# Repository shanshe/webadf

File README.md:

# webadf

An Amiga disk library that puts a disk in a real Amiga's floppy drive over WiFi.

Two halves that work together:

- **A web app** for keeping Amiga disk images. Upload them, have them identified
  against TOSEC, OpenRetro and Demozoo, organise them into collections, browse and
  edit the files inside a disk, and rewind a disk to any earlier version.
- **A drive replacement.** An RP2350 board plugs into the Amiga's floppy connector,
  behaves like a DD or HD floppy drive, and plays whichever disk you pick in the web app.
  When the Amiga saves, the changes go back to the library.

Pick a disk in the browser, or tap its NFC tag on the drive, and the Amiga reads it.
Workbench 3.1 boots from the board, games load, and saves made on the Amiga show up
in the web app as new versions of the disk.

*Rev B, designed by Shanshe: 34-pin floppy header, floppy power connector, OLED
display, buzzer, a 4-pin header (J4), and a Pimoroni Pico Plus 2 W.
The KiCad project is in `wifi-floppy/hardware/`; check it with `pnpm hw:verify` before
ordering. The current bench board is rev A2.*

## Features

### Library

- Upload `.adf`, `.adz`, `.dms` and `.hfe`; drop `.lha` and `.zip` archives onto a disk
  to pick files out of them.
- HD (1.76 MB) ADFs are recognised and tagged HD, and are disks like any other: browsed
  and edited in the browser, with full history. Blank HD disks can be made from the
  New disk panel.
- Each unique disk is stored once, however many times it is uploaded.
- Disks are identified against TOSEC, OpenRetro and Demozoo, and grouped into titles
  with cover art, screenshots, publisher, year and type.
- Collections, search as you type, and a layout that works on a phone.
- Create a blank formatted disk: 880 KB or 1.76 MB, OFS or FFS.
- Download any disk as an ADF.

### Inside a disk

- Browse the AmigaDOS filesystem in the browser: files, folders, free space.
- Add, rename, move and delete files and folders; drop a folder from your computer
  onto a disk; drag entries between folders.
- Every change is a new version. The history panel shows what changed in each
  version, lets you browse any old version, and restores one as a new version.
- HFE images (including long-track formats such as Turrican's) play read-only and can
  be extracted to an ADF when every sector decodes.

### The drive

- Set up from a phone: the board opens a WiFi setup page, you enter your network and
  a pairing code from the web app, and it joins your library.
- Mount and eject from the web app, from the drive chips in the header, or by
  tapping an NFC tag.
- Reads and writes on a real Amiga. Saves reach the library as new disk versions,
  including saves made while the board was offline.
- Works as DF0 or alongside a second drive as DF1.
- Plays HD disks: the board tells the Amiga it is an HD drive while an HD disk is in.
  Needs Kickstart 3.0 or later. Playing needs firmware 1.4.1 or later (the web app
  refuses to mount an HD disk on older firmware and says so); saving to an HD disk
  needs 1.5.0 (1.4.x keeps HD write-protected on the board whatever the web app
  says).
- Write protection can be switched from the web app while the disk is in the drive.
- OLED status display: WiFi strength, what it is doing, the disk's name and the
  current track. An activity LED blinks on reads.
- Updates its own firmware from the web app. Releases are signed, a failed update
  falls back to the previous firmware, and the board never updates while a disk is
  in the drive.

### NFC tags

- Tap a tag on the drive to mount its disk. Tapping another tag swaps disks; tapping
  the one already in the drive does nothing.
- Write any disk to a tag from its library card or game page: click the NFC icon,
  tap a tag on the drive, and the result appears in the browser.
- A tag only ever mounts disks from your own library.
- Reader: HW-147C (Si512), on the board's I2C bus next to the OLED.

## How it works

An Amiga floppy drive does not deliver blocks. It hands Paula a raw magnetic flux
stream and the Amiga decodes MFM in software, so a drive emulator has to produce flux
at the right rate, continuously, while the disk spins.

```
  browser  ──mount──▶  web app  ──encodes ADF → MFM──▶  device  ──flux──▶  Amiga
     ▲                    │                                │
     └──── new version ◀──┴── Postgres + blobs     RP2350 + 8 MB PSRAM ◀── NFC tag
```

The server encodes a 901,120-byte ADF into 2,027,536 bytes of Amiga MFM and the board
streams it: PIO emits 2 µs bitcells, DMA restarts each revolution and raises INDEX,
giving 300 rpm. The whole disk lives in PSRAM, so a seek is answered immediately
instead of over the network. The board streams flux rather than ADFs, which lets
flux formats such as HFE use the same path.

An HD disk is the exception. The server sends the board the ADF itself (a small
WFAD header, then 1,802,240 bytes), and the board encodes each track to MFM as the
head reaches it, in about 4 ms, well inside the head's settle time. A PIO program
answers the Amiga's drive-ID read on RDY with the HD ID while an HD disk is mounted.
When the Amiga saves to an HD disk, the board checks all 22 sectors of the written
track, keeps them as ADF bytes, and uploads those bytes as they are.

When the Amiga writes, the board decodes the written tracks, uploads them, and the
server records them as a new version of the disk. Versions are stored as sector
deltas.

## Status

| | |
|---|---|
| Web app: library, collections, identification, search | live |
| Upload `.adf` `.adz` `.dms` `.hfe`; `.lha`/`.zip` onto a disk | live |
| File editing inside a disk, blank disks, drag and drop | live |
| Disk history: browse and restore any version | live, restore verified on hardware |
| Device: setup portal, WiFi, TLS, pairing | verified on hardware |
| Mount and eject from the browser and the drive chips | verified on hardware |
| Reading on a real Amiga (Workbench 3.1, games) | verified on hardware |
| Writing on a real Amiga, saves reach the library | verified on hardware |
| Second drive (DF1) alongside the board | verified on hardware |
| HFE, including long-track (Turrican) | verified on hardware; weak-bit titles not yet tested |
| HD disks, read-only (Kickstart 3.0+) | verified on hardware (firmware 1.4.1, Kickstart 3.1) |
| HD disks: Amiga saves, history, browser editing, blank HD disks | built and host-tested (firmware 1.5.0, not yet published); bench checklist owed (HANDOFF 3ao) |
| Firmware updates from the web app | verified on hardware (current: 1.3.1; 1.4.0 built, not yet published) |
| NFC: tap to mount, write tags from the web | verified on hardware |
| Rev B board | in design (Shanshe) |

## Repository

| Path | What |
|---|---|
| `src/` | the Next.js app |
| `src/lib/adfmfm/` | ADF ⇄ Amiga MFM encoder, verified against Greaseweazle |
| `src/lib/adffs/` | AmigaDOS filesystem reader/writer (OFS/FFS) |
| `src/lib/archive/` | `.lha`, `.zip` and `.dms` decoders, all browser-side |
| `src/lib/hfe/` | HFE parsing, conversion for the board, ADF extraction |
| `src/lib/disk-history/` | sector deltas and the version chain behind history and restore |
| `src/lib/nfc/` | NFC tap and tag-writing rules and storage |
| `wifi-floppy/firmware/` | the RP2350 firmware (pico-sdk ≥ 2.3.0) |
| `wifi-floppy/hardware/` | the board (KiCad) |
| `docs/superpowers/specs/` | design specs, one per feature |
| `HANDOFF.md` | the engineering log: decisions, measurements, bench results |

## Running it

```bash
pnpm install
pnpm dev                  # needs .env.local: DATABASE_URL, BLOB_READ_WRITE_TOKEN,
                          # BETTER_AUTH_SECRET, BETTER_AUTH_URL
pnpm test                 # vitest, pure logic
pnpm e2e                  # playwright, against a real database
```

Firmware:

```bash
export PICO_SDK_PATH=/path/to/pico-sdk        # tag 2.3.0 or later
pnpm firmware:build
pnpm firmware:test                            # host tests, no board needed
pnpm firmware:publish --dry-run               # sign and register a release
```

Write a disk to an NFC tag from the command line:

```bash
pnpm nfc:write "Turrican II disk 1"           # then tap a tag on the drive
```

The setup access point uses the password **`wififloppy`** by default. Set
`PORTAL_AP_PASSWORD` at build time to change it. The pairing code from the web app is
what authorises a board to join a library.

Every push that touches the firmware is built by
[`.github/workflows/firmware.yml`](.github/workflows/firmware.yml), which runs the host
tests and publishes a `.uf2` with a `manifest.json` (version, commit, size, SHA-256).

## Verification

Each layer that talks to hardware or to an undocumented format is checked against an
independent implementation:

| | checked against |
|---|---|
| `pnpm adfmfm:diff` | Greaseweazle's `amigados` codec |
| `pnpm adffs:verify` | `xdftool` |
| `pnpm lha:verify` | the real `lha` binary |
| `pnpm dms:verify` | xDMS, the implementation ours was ported from |

## Licence

- **Software** (the web app, scripts and the wifi-floppy firmware source): [MIT](LICENSE).
- **Hardware** (`wifi-floppy/hardware/`, the board design): [CERN-OHL-P-2.0](wifi-floppy/hardware/LICENSE), the
  permissive open-hardware licence, so anyone can build, modify and sell their own boards. The rev B PCB layout is
  Shanshe's work, licensed this way with Shanshe's agreement; see
  [wifi-floppy/hardware/NOTICE.md](wifi-floppy/hardware/NOTICE.md).
- **Third-party code, the libraries in the firmware image, and acknowledgements**: see
  [THIRD-PARTY-NOTICES.md](THIRD-PARTY-NOTICES.md). The Wi-Fi driver bundled with the Pico SDK is licensed for use
  on Raspberry Pi chips (which this board is).

This project builds on Nano-Tek, OpenFlops, Keir Fraser's FlashFloppy and Greaseweazle, and the other work credited
in the notices file.

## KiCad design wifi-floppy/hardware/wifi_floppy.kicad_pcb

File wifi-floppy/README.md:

# WiFi Floppy Emulator (Amiga) — Pico 2 W

Gotek-style drive replacement that streams pre-encoded MFM tracks over
WiFi from your ADF webservice instead of reading a USB stick.

## Contents
- `hardware/schematic.svg` — full schematic (net names match the PCB)
- `hardware/wifi_floppy.kicad_pcb` — placed **and routed** 2-layer board,
  45°-only corners, B.Cu ground pour. Open directly in KiCad 7/8 and
  press `B` to refill the zone.
- `hardware/generate_pcb.py` — the generator that produced the board,
  including a DRC-lite checker (crossings, clearance ≥0.15 mm, 45° rule).
  Currently passes with 0 violations.
- `firmware/` — pico-sdk project (RP2350 / `PICO_BOARD=pimoroni_pico_plus2_w_rp2350`,
  pico-sdk >= 2.3.0 required — see "Firmware build requirements" below).

## Design
- **J1** 34-pin, Amiga internal pinout: pin 2 = /DSKCHG, pin 34 = /RDY
  (unlike PC drives where 34 is DSKCHG).
- **U2 74LVC541A** buffers all host-driven lines into the Pico
  (3.3 V part, 5 V-tolerant inputs). J1→A1..A8→GP2..GP9 are mapped in
  physical order, so the input routing is completely crossing-free.
- **Q1–Q6 BSS138** give open-drain outputs. They invert: **GPIO high =
  bus line pulled low**. Firmware and the PIO program already account
  for this (`OUT_ASSERT`).
- **Power**: 5 V from the Berg connector through D1 (SS14) into VSYS.
  Safe to co-power over USB while bench testing.
- PIO `flux_out` emits 2 µs bitcells (8 PIO cycles @ 4 MHz, clkdiv 37.5
  from 150 MHz), 750 ns read pulses; DMA restarts per revolution and
  raises a ~2 ms INDEX pulse at the wrap → exactly 300 rpm timing.
- 16-track LRU cache (~205 KB) + neighbour prefetch; a track is ~12.7 KB
  so a LAN fetch lands well inside a seek's settle time.

## Track server protocol — SUPERSEDED

**This section describes a protocol the firmware no longer speaks.** `http_fetch.c`,
which implemented `GET /tracks/<n>`, was deleted in plan 4a. The real device contract is
`GET /api/device/poll` (long-poll for desired state), `GET /api/device/image/<sha256>`
(the whole disk as a `WFMF` container, format defined in `image_loader.c`), and
`POST /api/device/status`. See `INTEGRATION.md` and
`docs/superpowers/specs/2026-08-29-device-plane-disk-change-design.md` §10 for the actual
contract. Kept below only as a historical note; do not implement against it.

```
GET /tracks/<n>        n = cyl*2 + side  (0..159)
 -> 200, body = [u32 LE bit_count][raw MFM bytes]
POST /tracks/<n>       (write-back, not implemented yet)
```
Encode server-side (ADF → Amiga MFM incl. 0x4489 syncs, odd/even split);
the firmware just plays bits. Suggested next step for the webservice.

## DSKCHG / RDY
`src/dskchg.c` re-implements FlashFloppy's Amiga-interface behaviour
(chgrst=step semantics, motor-edge drive-ID shifter, spin-up delay).
It's a from-scratch implementation of the observable behaviour, not a
code port. FlashFloppy is Keir Fraser's (https://github.com/keirf/flashfloppy,
Unlicense) and is credited in ../THIRD-PARTY-NOTICES.md.

## Firmware build requirements

- **pico-sdk >= 2.3.0.** `hardware_psram` (and this board's
  `PICO_PSRAM_CS_PIN`/`PICO_PSRAM_SIZE_BYTES` board-header support) landed in
  pico-sdk PR #2919, after the 2.2.0 release; 2.3.0 is the first tag that has
  it. `CMakeLists.txt` checks `PICO_SDK_VERSION_STRING` and fails the
  configure step with an explanation if `PICO_SDK_PATH` points at anything
  older.
- **`brew install arm-none-eabi-gcc` is not sufficient** — that formula ships
  GCC and libgcc but no newlib, so linking fails with `cannot find -lg`/`-lc`
  on the very first target. Use the official ARM GNU Toolchain instead (the
  `gcc-arm-embedded` cask, or the equivalent tarball from
  developer.arm.com/downloads/-/arm-gnu-toolchain-downloads) and make sure
  its `bin/` is on `PATH` ahead of any homebrew `arm-none-eabi-*` shims.
- **`PORTAL_AP_PASSWORD` must be set in the environment (plan 4b).** It becomes the WPA2
  PSK for the provisioning access point (see "Provisioning a board" below); CMake's
  configure step fails on purpose if it is unset or empty, because an invalid WPA2 PSK
  cannot be reported back to a console-less board at runtime. The full build command:

  ```bash
  export PATH="/Applications/ArmGNUToolchain/15.3.rel1/arm-none-eabi/bin:$PATH"
  export PORTAL_AP_PASSWORD=<your AP password>
  pnpm firmware:build
  ```

## Provisioning a board (plan 4b)

**Steps 1-3 are verified on hardware as of 2026-09-10; steps 4-5 are not.** The AP
comes up, iOS raises the sign-in sheet on its own, and the form renders at
192.168.4.1. Everything from pressing Save onwards — teardown, association,
registration — has still only ever run against the host suite. See "Honest caveats"
below.

A board with no WiFi credentials stored in flash — or one that has just failed to associate
three times in a row — raises its own WPA2 access point named `wifi-floppy-XXXX`, where
`XXXX` is the last two octets of the board's MAC address (so several boards on a bench stay
distinguishable). To provision it:

1. **Mint a pairing code in webadf.** From the web app, generate a device pairing code for
   the board (single-use, 10-minute TTL — if it expires before step 4, generate a new one).
2. **Join `wifi-floppy-XXXX`** from your phone or laptop, using the WPA2 password baked into
   that board's firmware image at build time (`PORTAL_AP_PASSWORD`, above — whoever built
   the firmware knows it).
3. **Open any page** in a browser on that device. The board's DNS responder answers every
   query with its own address and the HTTP server redirects every path to `/`, so a phone's
   captive-portal probe should bring the config form up on its own; if it does not, browse to
   `http://192.168.4.1/` directly.
4. **Enter three fields**: your real WiFi network's SSID, its password, and the pairing code
   from step 1. Submitting does not commit anything yet — the board drops its own AP,
   attempts to associate with what you typed, and only writes the credentials to flash on
   success. Your phone will briefly lose the `wifi-floppy-XXXX` network while this happens.
5. **On success**, the board joins your real network and proceeds to register with webadf
   using the pairing code; the AP does not come back. **On failure** (wrong password, or the
   network was not found — the form distinguishes the two), the AP returns with the reason
   and the form is ready to try again; re-enter all three fields, since none are echoed back.

**Recovery without reflashing.** If webadf later reports the board's token as revoked or the
device row is deleted, the board erases its stored token and returns to step 1 automatically
— generate a fresh pairing code and repeat steps 2–5. The same is true of a rejected
(expired or already-used) pairing code: the board returns to the portal rather than retrying
the dead code forever.

## Watching the log

```bash
tio /dev/cu.usbmodem*          # brew install tio; it reconnects across reboots
```

Output looks like this — uptime in seconds.milliseconds, then which core:

```
[    0.002] c0 wifi-floppy boot: pimoroni_pico_plus2_w_rp2350
[    0.481] c1 radio up (RM2)
[    0.494] c1 portal: raising AP
[   34.117] c0 MOTOR        a=1 b=0
[   34.119] c0 SEL          a=1 b=0
[   34.226] c0 STEP         a=1 b=0
[   34.229] c0 TRACK-SERVED a=2 b=101376
[   34.431] c0 INDEX        a=3168 b=0
```

Two entry points, and the difference is load-bearing. `wf_logf()` formats with
`vsnprintf` and is for core1 and core0's loop. `wf_trace()` takes an integer event code
and two integers — no formatting, no format string — so it is legal inside the flux DMA
handler, where a flash-resident string would not be. `wf_trace` is placed in SRAM with
`__not_in_flash_func` for the same reason `dma_irq` is.

**core0 drains, core1 only produces.** core0's service loop already sleeps 1 ms per
iteration and the bit-level work is PIO and DMA, so it has the slack to write to USB;
core1's loop blocks for tens of seconds inside a long-poll and would strand every core0
trace behind it. A useful consequence: a core1 hang still gets its last line out, which
is why `cyw43_arch_init` failing logs before it spins forever.

The ring holds 63 records (~7 KB of SRAM). When it fills it **drops newest and counts
them**, then prints `-- N record(s) dropped --` once the backlog clears. It never blocks
a producer: a logger that stalls the floppy service loop to report on the floppy service
loop would be worse than no logger. `PICO_STDIO_USB_STDOUT_TIMEOUT_US` is set to 1 ms in
`CMakeLists.txt`, against an SDK default of 500 ms, so an unattended USB port cannot
stall that loop either.

UART stdio stays off and must stay off: GP0 and GP1 are INDEX and CHNG on this board, so
enabling it would drive the floppy bus.

## Honest caveats
- **First run on real hardware: 2026-09-10.** A rev A2 board, partially populated
  (J1, J2 and U1 only), flashed with `wifi_floppy.uf2` and powered over USB. What that
  exercised, end to end, on real silicon:
  - the RP2350 boots the image, reaches `main()`, and launches core1
  - `cyw43_arch_init()` succeeds — the **RM2 radio works over SPI**, the single
    largest never-before-run piece
  - the AP comes up: `wifi-floppy-6A38`, WPA2-AES, SSID built from the chip's own MAC
  - **DHCP hands the phone an address, the DNS responder answers, and the HTTP server
    serves the form** at `192.168.4.1`
  - **iOS's captive-portal probe raises the sign-in sheet on its own** ("Wi-Fi med
    tilmelding"), which was explicitly on the unverified list
  - the page's `28:cd:c1:19:6a:38` and the SSID's `6A38` agree, so `main.c`'s
    `mac_address_string()` and `portal_net.c`'s SSID construction cross-check
  - no re-enumeration of the USB CDC device over several minutes: no crash loop

  **Still not run on hardware:** everything past pressing Save. AP teardown and the
  transition back to station mode, association with a real network, the confirmation
  page arriving before the AP drops, DHCP lease renewal after teardown, the 3-slot
  lease pool under real phone behaviour, Android's captive-portal probe, TLS, SNTP,
  device registration, and the whole floppy side — PIO cycle counts, DMA, PSRAM image
  load, bus timing — which remain desk-checked only. See
  `docs/decisions/2026-08-31-device-portal-rulings.md`'s hardware-only list for the
  full set, which plan 5 owns closing.
- **Console logging exists as of 2026-09-10 (`src/wf_log.c`), but has not itself run on
  hardware.** Before it, the firmware wrote nothing at all: `stdio_init_all()` brought up
  the CDC device so a port appeared and a terminal attached, but there was not one
  `printf` in `src/`, and listening returned zero bytes. See "Watching the log" below for
  how to use it. Host-tested (74 checks) and cross-built clean; every line it prints on a
  real board is still unobserved.
- It compiles (`pnpm firmware:build` produces `firmware/build/wifi_floppy.uf2`) and has
  a green host suite (`pnpm firmware:test`, 506 checks across 13 binaries, plain C under
  clang). Treat anything not covered by a host test or by the hardware run above as
  unverified.
- Write support is a skeleton: flux capture PIO exists, MFM decode and
  POST are TODO. WPROT is asserted by default until that lands.
- The board passes my generator's DRC-lite, but run real KiCad DRC and
  sanity-check footprints (Pico row spacing 17.78 mm, SOIC-20W, SOT-23)
  against your parts before ordering.
- No mounting holes; outline is a plain 96×62 mm rectangle. Reshape to
  3.5"-drive dimensions if you want it inside a Gotek/drive bay.
- Board is 2-layer; several signals ride the B.Cu plane, which slices
  the pour locally. Fine at 500 kHz MFM rates, but keep the pour filled.

## PSRAM revision (Pimoroni Pico Plus 2 W)

U1 is now specified as a **Pimoroni Pico Plus 2 W** (RP2350B, 16MB flash,
8MB PSRAM, RM2 radio). It keeps the Pico footprint and pinout, so the PCB is
unchanged electrically - only the module value differs.

PSRAM is the disk. The image is pulled in **one bulk transfer at mount**
(`image_loader.c`) and the floppy bus is served entirely from RAM after
that - the read path contains no network call at all.

| where | size | role |
|-------|------|------|
| SRAM double buffer | ~26 KB | only DMA source for the flux PIO |
| PSRAM disk image | 2.03 MB | the whole disk, 160 x 13 KB slots |

**The route below is superseded** — the firmware fetches
`GET /api/device/image/<sha256>` (keyed by digest, not an integer id; see
`INTEGRATION.md` and disk-change spec §10), but the `WFMF` container body format
itself is current and matches `image_loader.c`:

    u32 magic 'WFMF'   u32 version=1   u32 track_count   u32 reserved
    per track: u32 bit_count, ceil(bits/8) bytes, padded to 4 bytes

RDY and CHNG stay deasserted until the whole image is in PSRAM, so a slow or
failed load looks like "no disk yet" to the Amiga rather than a drive that
stalls mid-track. A track missing from PSRAM is a fault, not a cache miss:
`track_cache_get()` returns NULL and nothing is streamed.

The loader parses the blob incrementally as TCP chunks arrive, writing
straight into PSRAM (a 2 MB image never fits in SRAM). It was tested on the
host against randomly-chunked input at real track sizes, plus malformed
input: oversized tracks and bad magic are rejected without overflowing a slot.

Notes / still to verify on hardware:

* **GP0/GP1 are the board's default UART pins** and carry INDEX and CHNG here.
  `pico_enable_stdio_uart(... 0)` is set; stdio goes out over USB. Do not
  re-enable UART stdio or it will drive the floppy bus.
* The flux DMA never reads PSRAM directly - a QMI cache miss contending with
  XIP can add latency at a 2 us bitcell. Tracks are copied PSRAM -> SRAM.
* **Antenna keepout position is still an assumption, and the PIM726 documents
  do not settle it.** A schematic carries no placement, and the "Pins and
  Dims" sheet's board illustration is not something to read a fab decision
  off. What the keepout currently claims, so it can be checked against a
  module in hand: it spans the module's full 21 mm width and the last 5.4 mm
  of its 51 mm length at the **non-USB end** - the pin 19-22 end, GP14-GP17.
  If the RM2's antenna is anywhere else, there is ground plane under it.
  Costs nothing to keep: GP14-GP17 are unused on this board, so the keepout
  is only wrong if it is in the wrong *place*, never merely expensive.
* ~~Confirm GP0-GP17 map to the same physical castellations on the RP2350B
  board as on the Pico 2 W.~~ **CONFIRMED 2026-09-09** against the PIM726
  schematic (sheet 3/3, "Output headers"). The Plus 2 W's header is the
  standard Pico header pin for pin: pin 1 = GP0 through pin 22 = GP17, with
  GND on 3/8/13/18/23. The only difference is that pins 6 and 7 are labelled
  `GP4_SDA` and `GP5_SCL` because they also feed the QW/ST connector - same
  GPIOs, alternate function. Every U1 signal this board uses lands where it
  was assumed to.
* Write-back path is still a skeleton: PSRAM now has TRK_DIRTY state and
  `psram_image_next_dirty()` for a flush walker, but nothing calls it yet.

## J1 floppy header - construction

J1 is a **male 2x17 through-hole pin header on 2.54 mm pitch** (both axes),
which is what a standard 34-way floppy ribbon with female IDC sockets on each
end plugs onto - same as a real 3.5" drive or a Gotek.

* Numbering is standard IDC dual-row: pin 1 and 2 adjacent across the rows,
  odd pins down one column, even down the other.
* All odd pins (1..33) are GND, matching the ribbon's alternating ground
  returns. Signals are on the even pins.
* Pin 1 now has a **square pad**, plus a silkscreen body outline and a
  chevron marker outside pin 1, so the red stripe end is unambiguous.
* Pads 1.7 mm with 1.0 mm drill - correct for the usual 0.64 mm square posts.

**Shrouded header is not a drop-in.** A keyed 2x17 IDC box header has a
10.16 mm body, which overhangs the FET drain pads by ~1.35 mm. To fit one,
the Q1-Q6 column must move about 2 mm east, which also pushes the input
routing channels. The plain header is what most drives use, so rev B keeps
it; polarity relies on the pin-1 markings and the cable's red stripe.

## Revision history - rev B is current

| rev | state |
|-----|-------|
| A   | fabricated, **scrap** - every layer mirrored, and four SOT-23s reflected |
| A2  | fabricated, **usable with a caveat** - correct except that the ground pour runs under the RM2 antenna |
| B   | **current**, not yet fabricated - A2 with the antenna keepout at the right end; copper, mask, drill and outline are byte-identical to A2 |

### Rev A2 errata - rev A boards are scrap

The first batch (rev A) came back from JLCPCB mirrored and cannot be used.
Two independent bugs, both now fixed and both now covered by
`hardware/verify_board.py`, which must be run before any future fab order.

**1. Gerber Y axis.** KiCad's coordinate system has Y increasing downward;
Gerber and Excellon have Y increasing upward, and KiCad negates Y when it
plots. `export_gerbers.py` wrote coordinates straight through, so every
layer was reflected. The renderer used the same Y-down convention, so the
preview looked correct and the verification compared the Gerbers against an
equally wrong-handed source - self-consistent, and self-consistently
mirrored.

**2. SOT-23 gate/source.** Q1, Q2, Q3 and Q6 were reflections of the
canonical KiCad SOT-23 land pattern - gate and source swapped - so a real
part would have had its gate on the GND pad and never switched. Only Q4 and
Q5 were right. Independent of bug 1; it would have shipped either way.

Fixing 2 moved the gate and source pads, which made Q3's gate pad overlap
Q4's source pad, so Q3 moved 0.6 mm north and its drain now jogs to J1 row
13 the way Q2 and Q5 already did. The INDEX, TRK0, RDY and CHNG gate routes
were re-run to suit.

`verify_board.py` now checks every footprint against the canonical KiCad land
pattern (rotation = fine, reflection = fail) and confirms the Gerber pads sit
at the mirrored Y of the .kicad_pcb. Regression-tested against the old broken
export: it reports 118/122 pads at un-mirrored Y and fails.

**A2 follow-up: antenna keepout was at the wrong end.** The rev A2 boards
were fabricated with the ground pour void over U1 pins 1/2/39/40 instead of
19/20/21/22 - the opposite end of the module. Cause: `export_gerbers.py`
flipped Y for pads, traces, silk, outline and drill, but not for the keepout
zone polygon, so the void mirrored away from the antenna. The pour audit
missed it because it used the same unflipped polygon on both sides of the
comparison - self-consistent again. Fixed, and `verify_board.py` now asserts
the keepout covers U1 pins 19-22 - reading copper out of the emitted `.GBL`
rather than re-deriving the void from the exporter, so the check cannot agree
with the exporter's mistake the way the last one did. Regression-tested both
ways: it fails on the rev A2 `.GBL` (25/25 sample points copper under the
antenna) and passes on the current one (0/25).

Consequence for the rev A2 boards in hand: they are electrically fine (all 27
GND pads still bond, no signal pad is affected) but there is ground plane
under the RM2 antenna and a harmless void near pins 1/2. Build one and check
signal strength before respinning - the whole-image PSRAM load means WiFi only
has to work at mount time.

### Rev B

The corrected files are **rev B** and have not been fabricated. Copper, mask,
drill and outline are byte-identical to rev A2 - `.GTL`, `.GTS`, `.GBS`, `.GKO`
and `.TXT` all unchanged - so an assembled rev A2 board remains a valid bring-up
target and nothing in the BOM changes. Two files differ: `.GBL` for the keepout,
and `.GTO`, because rev B is the first revision whose silkscreen will print.

**Rev B is marked.** The board says `WIFI FLOPPY REV B` on the silkscreen and
carries its reference designators; rev A and rev A2 have neither, so an unmarked
board is one of the older two. Which of those it is you tell from the pour void:
on A2 it sits at the USB end of U1, on B at the opposite end.

### Rev A and rev A2 have outlines but no lettering

**Corrected 2026-09-09 from a photograph of an assembled rev A2 board.** An
earlier version of this section said the silkscreen never printed at all and
blamed the fab for stripping it. That was wrong, and it was wrong in the
direction that flatters the diagnosis: I inferred it from a spec table instead
of from the board. J2's and U1's body outlines are plainly legible on a real
board, at 0.12 mm. Two separate things are true:

1. **The exporter dropped everything that was not an `fp_line`, and that is why
   there is no lettering.** All 13 reference designators, the antenna-keepout
   label and U2's pin-1 dot never reached the `.GTO` at all - silently, because
   nothing counted what it skipped. `export_gerbers.py` now renders text through
   `stroke_font.py`, a single-stroke vector font, and draws circles.
2. **Every silk feature was also below the fab's published minimum**, which is a
   real DFM violation even though it printed. JLCPCB's minimum silkscreen line
   width is 6 mil (0.1524 mm); the outlines were 0.12 mm and the J1 chevron
   0.15 mm, so all 17 features were under it. They came out this time. A layer
   that prints only because the fab was lenient is not one to ship again, so rev
   B draws silk at 0.2 mm and text at 1.0-1.5 mm.

Neither was visible to any check, which is the third time something wrong in the
fab output got there because nothing was looking at it. `verify_board.py` now
reads feature widths back out of the emitted `.GTO` and fails on anything below
the fab minimum, and `export_gerbers.py` reports any legend stroke that lands
within 0.15 mm of a pad. Designator placement was moved to suit: the FET column
is on a 3.14 mm pitch, so Q1-Q6 label to the east rather than above.

### Orienting the parts

D1 is the only part you can silently fit the wrong way round, so rev B marks
it: a body outline closed at the cathode end, drawn with a heavier bar than
the sides. **The SS14's banded end goes to that bar** - pad 1, the pad whose
trace runs the long way up the board, away from J2. Pad 2 is the anode, fed by
the +5V run that comes along the bottom edge from J2.

Pad 1 is the cathode by what KiCad's own `D_SMA` draws, not by convention: its
`F.Fab` layer puts the diode symbol's bar on the pad-1 side with the triangle
pointing at it, and its `F.SilkS` outline closes that end. The netlist agrees -
pad 1 is `VSYS`, pad 2 is `+5V`, and current runs anode to cathode. Reversed,
the board simply will not power from the floppy connector while still working
over USB, which is an annoying thing to debug.

Everything else is keyed:

| part | how you orient it |
|------|-------------------|
| J1, J2, U1 | square pad 1 (J1 also has the chevron). U1 matters - a 2x20 header footprint is symmetric, so the module fits rotated 180 degrees |
| U2 | pin-1 dot on the silkscreen |
| Q1-Q6 | no marking, and none needed: SOT-23 has two pads one side and one the other, so it cannot land rotated |
| C1, C3 | ceramic, not polarised |

**Still unconfirmed:** that the RM2's antenna is at the pin 19-22 end at all.
That is inherited from the CYW43 Pico 2 W and has never been checked against a
PIM726 in hand. `verify_board.py` enforces the assumption; it cannot validate
it. Confirm before ordering rev B, because moving the void is the only thing
rev B does.

Component orders are unaffected - every part in the Mouser order is still
correct for rev A2 and for rev B.

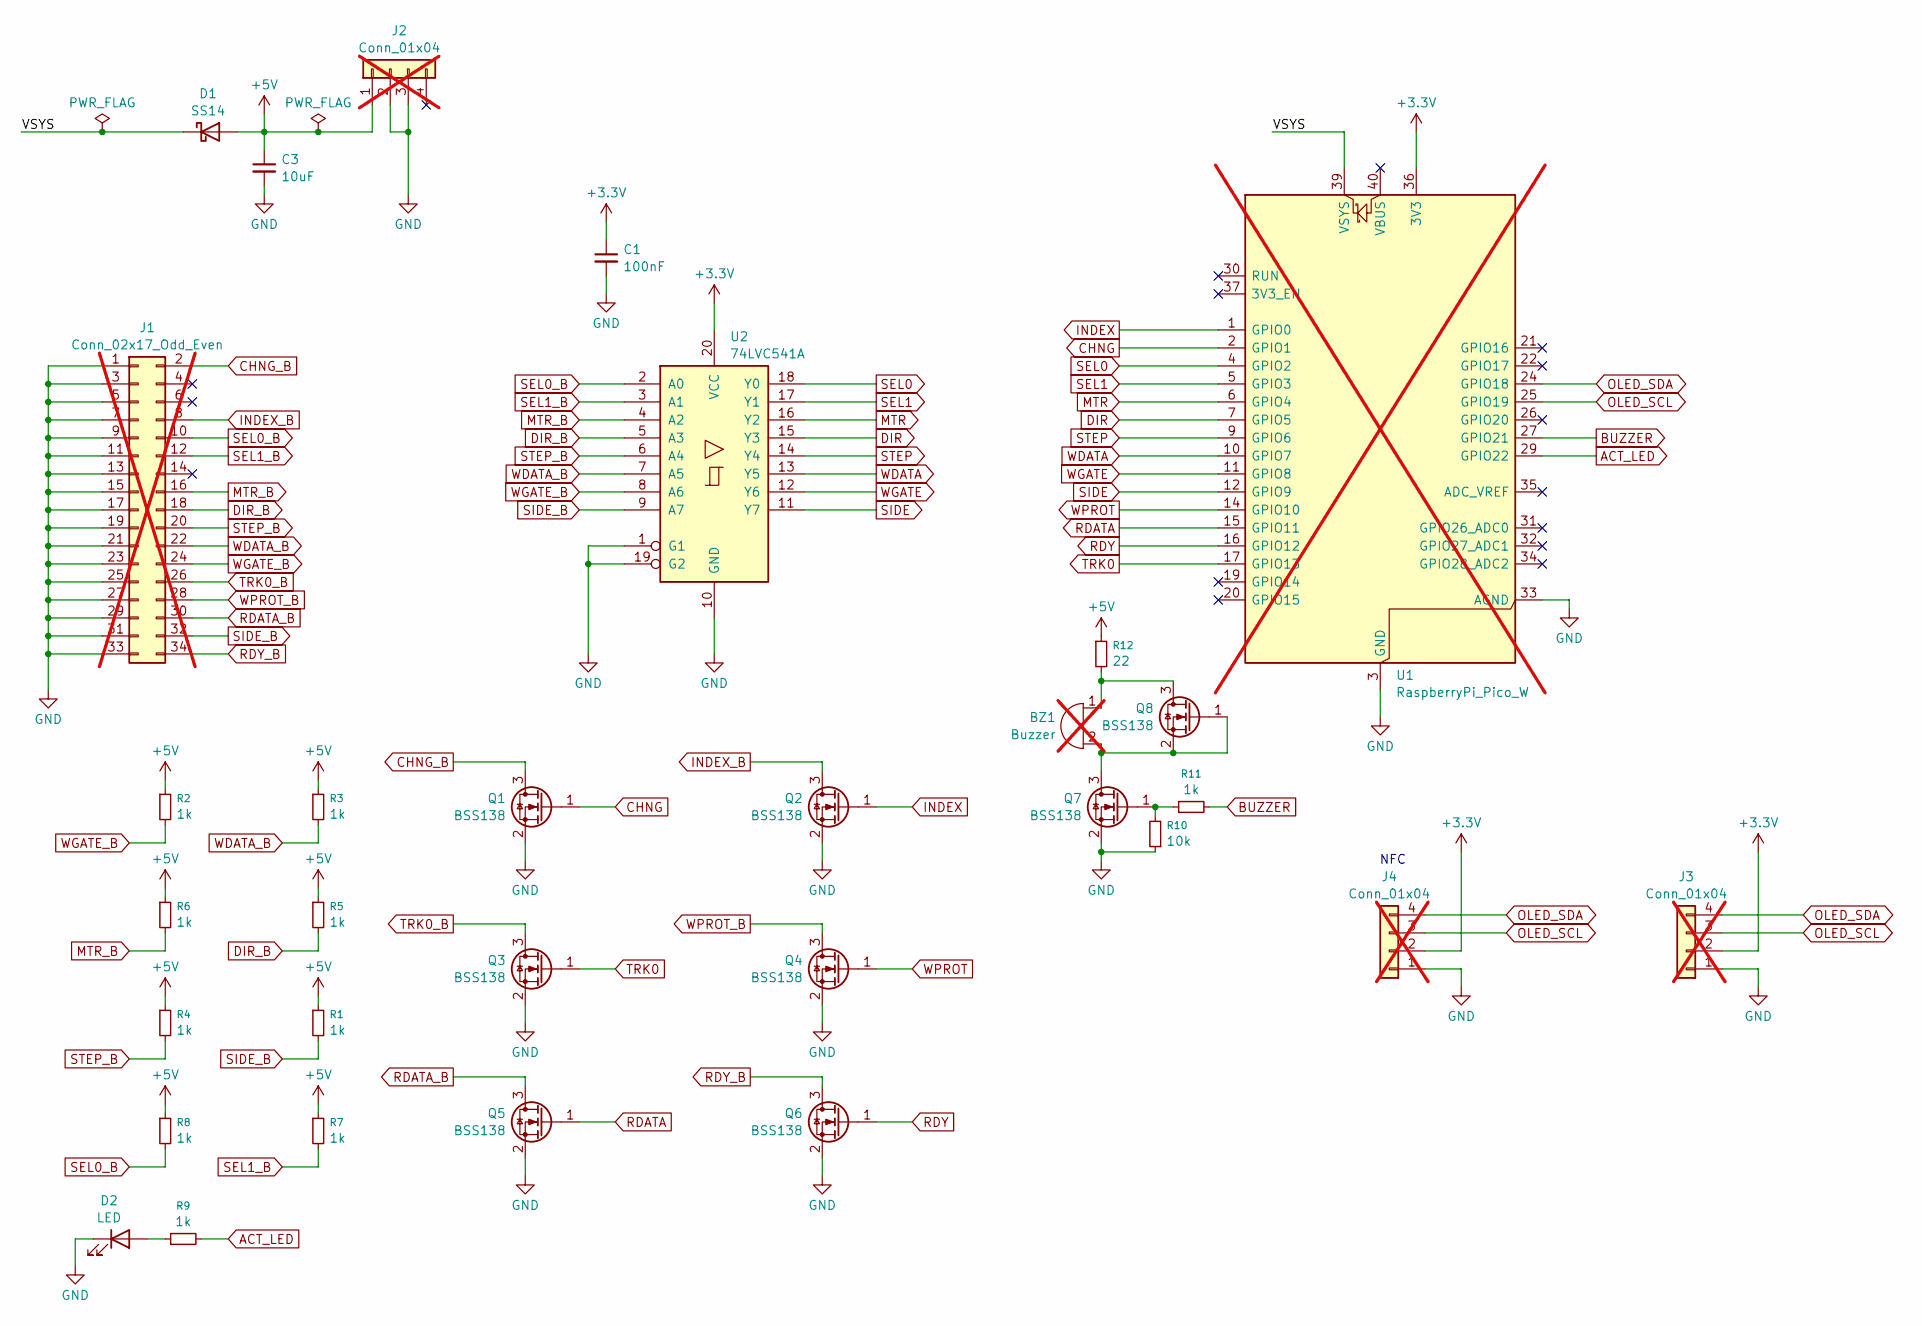
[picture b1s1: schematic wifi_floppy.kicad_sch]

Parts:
BZ1: Buzzer; Buzzer_TDK_PS1240P02BT_D12.2mm_H6.5mm; LCSC DNP; not fitted
C1: 100nF; C_1206_3216Metric_Pad1.33x1.80mm_HandSolder
C3: 10uF; C_1206_3216Metric_Pad1.33x1.80mm_HandSolder
D1: SS14; D_SMA_Handsoldering
D2: LED; LED_1206_3216Metric_Pad1.42x1.75mm_HandSolder; LCSC C49018
J1: Conn_02x17_Odd_Even; IDC-Header_2x17_P2.54mm_Vertical; LCSC DNP; not fitted
J2: Conn_01x04; PinHeader_1x04_P2.54mm_Horizontal; LCSC DNP; not fitted
J3, J4: Conn_01x04; PinHeader_1x04_P2.54mm_Vertical; LCSC DNP; not fitted
Q1, Q2, Q3, Q4, Q5, Q6, Q7, Q8: BSS138; SOT-23
R1, R2, R3, R4, R5, R6, R7, R8, R9, R11: 1k; R_1206_3216Metric_Pad1.30x1.75mm_HandSolder; LCSC C1469
R10: 10k; R_1206_3216Metric_Pad1.30x1.75mm_HandSolder; LCSC C1489
R12: 22; R_1206_3216Metric_Pad1.30x1.75mm_HandSolder; LCSC C2925020
U1: RaspberryPi_Pico_W; RaspberryPi_Pico_W_SMD_HandSolder; LCSC DNP; not fitted
U2: 74LVC541A; SOIC-20W_7.5x15.4mm_P1.27mm; LCSC DNP

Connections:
+3.3V: C1.1, J3.2, J4.2, U1.36 (3V3), U2.20 (VCC)
+5V: C3.1, D1.2 (A), J2.1, R1.1, R2.1, R3.1, R4.1, R5.1, R6.1, R7.1, R8.1, R12.1
/VSYS: D1.1 (K), U1.39 (VSYS)
ACT_LED: R9.2, U1.29 (GPIO22)
BUZZER: R11.2, U1.27 (GPIO21)
CHNG: Q1.1 (G), U1.2 (GPIO1)
CHNG_B: J1.2, Q1.3 (D)
DIR: U1.7 (GPIO5), U2.15 (Y3)
DIR_B: J1.18, R5.2, U2.5 (A3)
GND: C1.2, C3.2, D2.1 (K), J1.1, J1.3, J1.5, J1.7, J1.9, J1.11, J1.13, J1.15, J1.17, J1.19, J1.21, J1.23, J1.25, J1.27, J1.29, J1.31, J1.33, J2.2, J2.3, J3.1, J4.1, Q1.2 (S), Q2.2 (S), Q3.2 (S), Q4.2 (S), Q5.2 (S), Q6.2 (S), Q7.2 (S), R10.1, U1.3 (GND), U1.8 (GND), U1.13 (GND), U1.18 (GND), U1.23 (GND), U1.28 (GND), U1.33 (AGND), U1.38 (GND), U2.1 (G1), U2.10 (GND), U2.19 (G2)
INDEX: Q2.1 (G), U1.1 (GPIO0)
INDEX_B: J1.8, Q2.3 (D)
MTR: U1.6 (GPIO4), U2.16 (Y2)
MTR_B: J1.16, R6.2, U2.4 (A2)
unnamed: BZ1.1 (+), Q8.3 (D), R12.2
unnamed: BZ1.2 (-), Q7.3 (D), Q8.1 (G), Q8.2 (S)
unnamed: D2.2 (A), R9.1
unnamed: Q7.1 (G), R10.2, R11.1
OLED_SCL: J3.3, J4.3, U1.25 (GPIO19)
OLED_SDA: J3.4, J4.4, U1.24 (GPIO18)
RDATA: Q5.1 (G), U1.15 (GPIO11)
RDATA_B: J1.30, Q5.3 (D)
RDY: Q6.1 (G), U1.16 (GPIO12)
RDY_B: J1.34, Q6.3 (D)
SEL0: U1.4 (GPIO2), U2.18 (Y0)
SEL0_B: J1.10, R8.2, U2.2 (A0)
SEL1: U1.5 (GPIO3), U2.17 (Y1)
SEL1_B: J1.12, R7.2, U2.3 (A1)
SIDE: U1.12 (GPIO9), U2.11 (Y7)
SIDE_B: J1.32, R1.2, U2.9 (A7)
STEP: U1.9 (GPIO6), U2.14 (Y4)
STEP_B: J1.20, R4.2, U2.6 (A4)
TRK0: Q3.1 (G), U1.17 (GPIO13)
TRK0_B: J1.26, Q3.3 (D)
WDATA: U1.10 (GPIO7), U2.13 (Y5)
WDATA_B: J1.22, R3.2, U2.7 (A5)
WGATE: U1.11 (GPIO8), U2.12 (Y6)
WGATE_B: J1.24, R2.2, U2.8 (A6)
WPROT: Q4.1 (G), U1.14 (GPIO10)
WPROT_B: J1.28, Q4.3 (D)

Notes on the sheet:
NFC

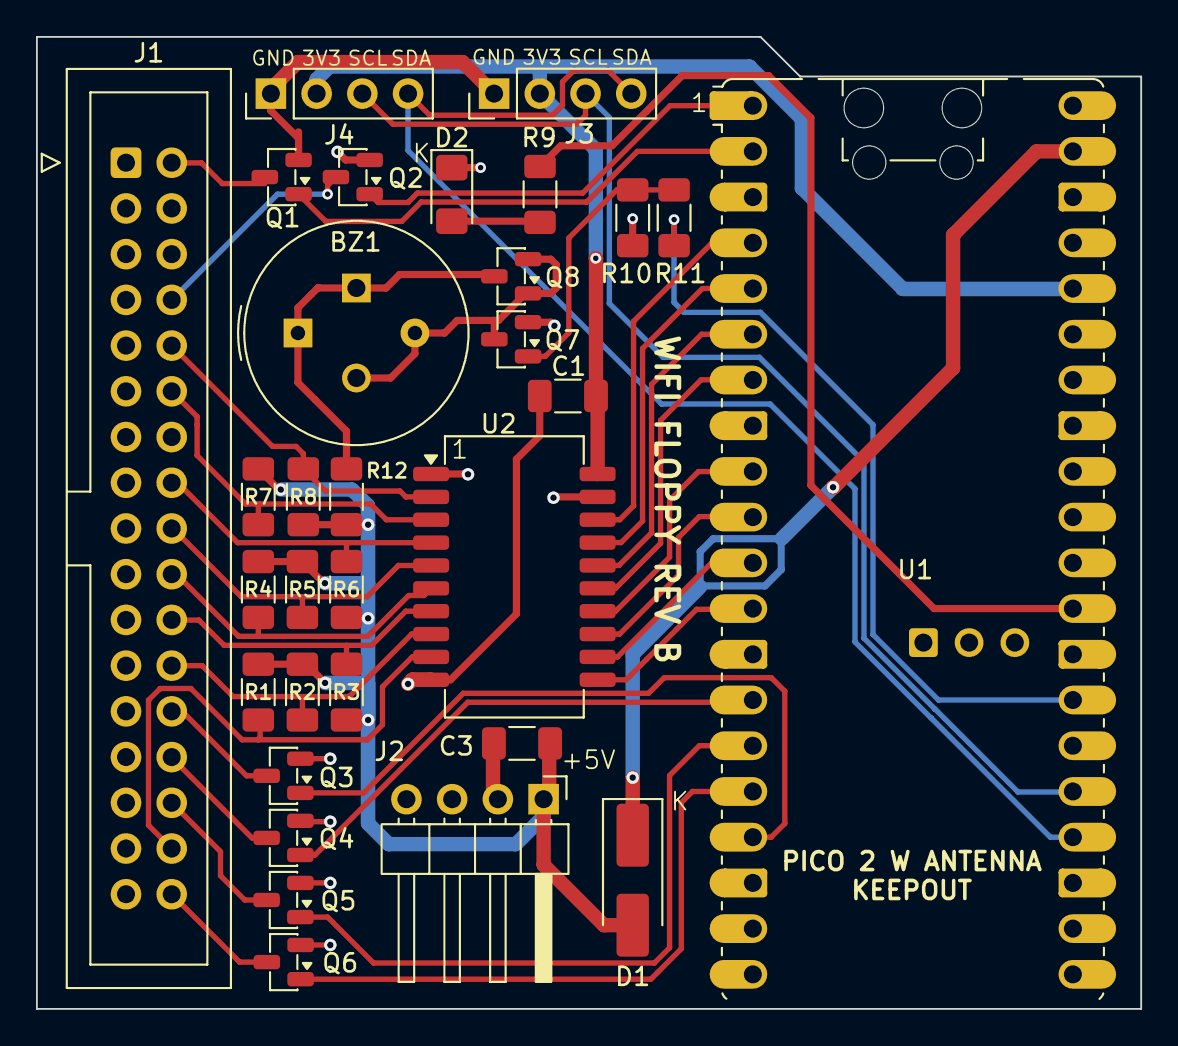
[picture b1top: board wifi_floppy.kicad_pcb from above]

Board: 2 copper layers, 61.4 x 54.0 mm, 31 parts (0 on the bottom side), 40 nets.

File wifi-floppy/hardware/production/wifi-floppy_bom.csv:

Designator,Footprint,Quantity,Value,LCSC Part #
BZ1,Buzzer_TDK_PS1240P02BT_D12.2mm_H6.5mm,1,Buzzer,DNP
C1,1206,1,100nF,
C3,1206,1,10uF,
D1,D_SMA_Handsoldering,1,SS14,
D2,1206,1,LED,C49018
J1,IDC-Header_2x17_P2.54mm_Vertical,1,Conn_02x17_Odd_Even,DNP
J2,PinHeader_1x04_P2.54mm_Horizontal,1,Conn_01x04,DNP
"J3, J4",PinHeader_1x04_P2.54mm_Vertical,2,Conn_01x04,DNP
"Q1, Q2, Q3, Q4, Q5, Q6, Q7, Q8",SOT-23,8,BSS138,
"R1, R11, R2, R3, R4, R5, R6, R7, R8, R9",1206,10,1k,C1469
R10,1206,1,10k,C1489
R12,1206,1,22,C2925020
U1,RaspberryPi_Pico_W_SMD_HandSolder,1,RaspberryPi_Pico_W,DNP
U2,SOIC-20W_7.5x15.4mm_P1.27mm,1,74LVC541A,DNP

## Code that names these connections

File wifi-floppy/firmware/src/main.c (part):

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static volatile int g_ui_status = DS_BOOT;
static volatile int g_ui_bars   = -1;
static volatile int g_ui_pct    = -1;
// Set from the SAME expression that drives the WPROT pin, never computed
// separately: a pencil that disagreed with the pin would be worse than no
// pencil, because it would be believed.
static volatile bool g_ui_writable = false;
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/*
 * WF_BUS_SNIFF -- log every change on the eight bus inputs, in exact order,
 * from the bus_sniff PIO program. Diagnostic, off by default
 * (-DWF_BUS_SNIFF=1). While it is on, the GPIO ISR's own SEL and SIDE traces
 * are suppressed: they carry the same edges, in pin order and sampled late,
 * and would only compete with these for log slots.
 */
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
// index pulse + wrap: retrigger DMA each revolution
static int64_t index_off(alarm_id_t id, void *ud) {
    bus_out_set(PIN_INDEX, false);
    return 0;
}
// Flash writes disable XIP. This handler re-arms the DMA each revolution and
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    if (!track_live) return;
    dma_channel_set_read_addr(dma_ch, track_words, false);
    dma_channel_set_trans_count(dma_ch, track_word_count, true);
    bus_out_set(PIN_INDEX, true);                    // ~2 ms index at wrap
    add_alarm_in_us(INDEX_PULSE_US, index_off, NULL, true);
    rev_count++;
    // ONCE PER STREAM, NOT ONCE PER REVOLUTION, and the difference is not
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    // DIRC high = towards 0
    if (outwards) { if (cur_cyl > 0) cur_cyl--; }
    else          { if (cur_cyl < NUM_CYL - 1) cur_cyl++; }
    bus_out_set(PIN_TRK0, cur_cyl == 0);
    dskchg_on_step();
    want_track = cur_cyl * 2 + cur_side;
    wf_trace(WF_EV_STEP, (uint32_t)cur_cyl, outwards ? 1u : 0u);
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// in progress from a settled one.
static volatile uint32_t g_write_last_ms;
static volatile uint32_t g_write_gen;
// Stamped in the WGATE ISR on both edges (see gpio_isr below) -- unlike
// g_write_last_ms, this marks the Amiga TOUCHING the write path at all, not
// only a capture that was later accepted. A torn/bad-checksum/wrong-track/
// overflowed capture never reaches g_write_last_ms, so without this the idle
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}

static void __isr gpio_isr(uint gpio, uint32_t events) {
    if (gpio == PIN_SEL0 && (events & GPIO_IRQ_EDGE_FALL)) {
        if (!WF_BUS_SNIFF) wf_trace(WF_EV_SEL, 1, 0);
    } else if (gpio == PIN_WGATE) {
        /*
         * The Amiga is writing. WGATE brackets exactly one track, so this is
         * the only signal that says when the flux on WDATA is worth anything.
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        // Both edges, unconditionally, before anything else in this branch --
        // see g_wgate_last_ms's comment. ISR: a volatile store only, no log.
        g_wgate_last_ms = clock_ms();
        bool writing = !gpio_get(PIN_WGATE);
        /*
         * Only DF0's writes. SEL0 is read here, at interrupt time, and that is
         * enough -- unlike STEP's DIR -- because the Amiga holds the drive
         * selected for the whole ~200 ms write, not for microseconds.
         */
        if (writing && gpio_get(PIN_SEL0)) {
            writes_other_drive++;
            return;
        }
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            flux_capture_disarm();
        }
        wf_trace(WF_EV_WGATE, writing ? 1u : 0u, (uint32_t)(cur_cyl * 2 + cur_side));
    } else if (gpio == PIN_SIDE) {
        cur_side = gpio_get(PIN_SIDE) ? 0 : 1;       // low = side 1
        want_track = cur_cyl * 2 + cur_side;
        if (!WF_BUS_SNIFF) wf_trace(WF_EV_SIDE, (uint32_t)cur_side, (uint32_t)want_track);
    }
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    static bool forced_logged;
    if (up_holds(up)) { if (decide) forced_logged = false; return true; }
    const bool motor_on = g_motor_on;
    const bool wgate = !gpio_get(PIN_WGATE);
    const uint32_t last_activity_ms =
        swap_gate_last_activity(g_write_last_ms, g_wgate_last_ms, motor_on, g_motor_on_ms);
    bool forced;
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            // HD writes spec §4.5: an HD disk follows the same three gates as
            // DD. (1.4.x held WPROT for HD whatever the server sent.)
            bool wprot = write_back_wprot(mounted, c.mounted_write_protected, up_forced);
            bus_out_set(PIN_WPROT, wprot);
            // The pin is set first, THEN the change is announced: the Amiga
            // must read the new state when it looks.
            if (reinsert_on_wprot(&reins, mounted, c.mounted_disk_id, wprot)) {
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    wf_log_init();
    wf_logf(WF_INFO, "wifi-floppy boot: %s", PICO_BOARD);

    // inputs. PIN_WDATA belongs here too even though only PIO reads it: an
    // RP2350 pad stays isolated from reset until gpio_set_function() clears
    // ISO, and until then PIO reads it as 0 whatever the pin carries. Left
    // out, WDATA read low in every sample, with 1k to +5V on J1 pin 22 and
    // the Amiga idle (2026-09-15).
    const uint ins[] = {PIN_SEL0, PIN_SEL1, PIN_MTR, PIN_DIR,
                        PIN_STEP, PIN_WDATA, PIN_WGATE, PIN_SIDE};
    for (unsigned i = 0; i < count_of(ins); i++) {
        gpio_init(ins[i]); gpio_set_dir(ins[i], GPIO_IN);
    }
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    // WPROT after this (see its WPROT comment), but "asserted" is the only
    // safe value to boot with regardless: read-only until proven otherwise
    // beats writable by default.
    bus_out_init(bus_pio, (1u << PIN_TRK0) | (1u << PIN_WPROT));

    dskchg_init();
    track_cache_init();
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    // PIO
    uint off_out = pio_add_program(pio, &flux_out_program);
    sm_out = pio_claim_unused_sm(pio, true);
    flux_out_program_init(pio, sm_out, off_out, PIN_RDATA, PIN_SEL0);
    pio_sm_set_enabled(pio, sm_out, true);

    uint off_in = pio_add_program(pio, &flux_in_program);
    sm_in = pio_claim_unused_sm(pio, true);
    flux_in_program_init(pio, sm_in, off_in, PIN_WDATA);
    // Claims a DMA channel and points it at sm_in's RX FIFO. The state machine
    // stays DISABLED until WGATE says the Amiga is writing -- see
    // flux_capture_arm().
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    // bus_pio above), and "pio claims" in the log says where it landed.
    uint off_step = pio_add_program(step_pio, &step_dir_program);
    step_sm = pio_claim_unused_sm(step_pio, true);
    step_dir_program_init(step_pio, step_sm, off_step, PIN_STEP, PIN_SEL0);
    pio_set_irq0_source_enabled(step_pio, pio_get_rx_fifo_not_empty_interrupt_source(step_sm),
                                true);
    irq_set_exclusive_handler(pio_get_irq_num(step_pio, 0), step_pio_isr);
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    // edge: MTR is shared, and only the selected drive takes it.
    uint off_mtr = pio_add_program(bus_pio, &sel_mtr_program);
    mtr_sm = pio_claim_unused_sm(bus_pio, true);
    sel_mtr_program_init(bus_pio, mtr_sm, off_mtr, PIN_SEL0, PIN_MTR);
    pio_set_irq0_source_enabled(bus_pio, pio_get_rx_fifo_not_empty_interrupt_source(mtr_sm),
                                true);
    irq_set_exclusive_handler(pio_get_irq_num(bus_pio, 0), mtr_pio_isr);
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    irq_set_enabled(pio_get_irq_num(bus_pio, 1), true);
    pio_sm_set_enabled(bus_pio, sniff_sm, true);
    wf_logf(WF_WARN, "BUS SNIFF BUILD: every bus change is logged "
                     "(a = GPIO mask, GP0..13 without WDATA/RDATA; bit 16 = samples dropped before)");
#endif

    gpio_set_irq_enabled_with_callback(PIN_SEL0, GPIO_IRQ_EDGE_FALL, true, gpio_isr);
    gpio_set_irq_enabled(PIN_SIDE, GPIO_IRQ_EDGE_FALL | GPIO_IRQ_EDGE_RISE, true);
    // Both edges: the falling one starts a capture and the rising one ends it,
    // and an end that is missed would run the ring into the next write.
    gpio_set_irq_enabled(PIN_WGATE, GPIO_IRQ_EDGE_FALL | GPIO_IRQ_EDGE_RISE, true);

    // NOT multicore_launch_core1(): that uses the SCRATCH_X-resident
    // .stack1_dummy, which tops out at 4 KB and cannot hold core1's
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            }
            bool forced;
            if (reinsert_may_announce(clock_ms(), g_reinsert_raised_ms, dskchg_motor_on(),
                                       !gpio_get(PIN_WGATE), last_activity_ms, &forced)) {
                // Read-then-clear, not atomic: if core1 raises a NEW request
                // between the `if` above and this store, it is lost here.
                // Harmless -- core1 always stores the new WPROT pad state
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        /*
         * REVERTED 2026-09-13, the same day it was written.
         *
         * This briefly sampled the SIDE pin here and required it to be stable
         * for one iteration, instead of taking want_track from the ISR. The
         * reasoning looked sound -- SIDE is a level the host holds, not a
         * pulse, and 3,725 edges under 1 ms apart had been measured -- but the
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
